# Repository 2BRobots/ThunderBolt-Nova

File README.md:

# ThunderBolt-Nova
Here can be found all the resources to build your own ThunderBolt development board. This board is based on the PIC18F14K50 microcontroller. It uses a bootloader so you can program it directly over USB without an ICSP programer. 
If you decide to make your own board you will need to burn the bootloader the firts time. You can use the 12Mhz or 48Mhz version, the hardware is the same for both versions.

Note: For the servo ports you must pay attention to the pin names in the botton of the board, not the top. Wiring in some servo models will require a modification. Also there is an error in silkscreen, in C5 servo port in the botton says "C2" instead of "C5". 
Be careful, this ports where designed to drive micro-servos. Using full size (8kg.cm or greater) servos can destroy the board due to excesive current flow, please use external power for the servos in this case.  

In this repositiry are all resources, examples and design files that will allow you to use all features of the board.

Here is a video of how to get started:

https://youtu.be/WCGcCIe8bug

Voltage Pinout:
GND = voltage ground.
EN  = this is the signal from the on/off switch, can be used for turn on/off addon boards.
VU  = this are the 5v from the USB port.
VB  = this is the voltage from the battery.
3V  = This is the regulated 3v output, it only can supply 200mA.

Also there is a shared pins for the internal LED (B7) and button (A3), this are used in the bootloader program but you can use it in your program too!!!  As an extra there is a voltage divider shared in the pin C6 (AN8) to measure the lipo battery voltage. 
For full diagram of conections and specs please see the board schematic and microcontroller datasheet. 

This board was designed to use a 1S litium battery (3.7v) and is equiped with an on board battery charger. Be careful when using one, wrong polarity can destroy your board!!!

Hope you find it useful and can make a lot of projects with it.

2B Robots (DAFR Electronics) invests time and resources providing this open source code and hardware, if you valorate our hard work please purchase our products and support us to continue creating more open source products!!!

Hardware licensed with Creative Commons BY-NC-SA.

Created by Daniel A. Fernandez Raygoza for 2B Robots.

Visit our online store: www.2brobots.com

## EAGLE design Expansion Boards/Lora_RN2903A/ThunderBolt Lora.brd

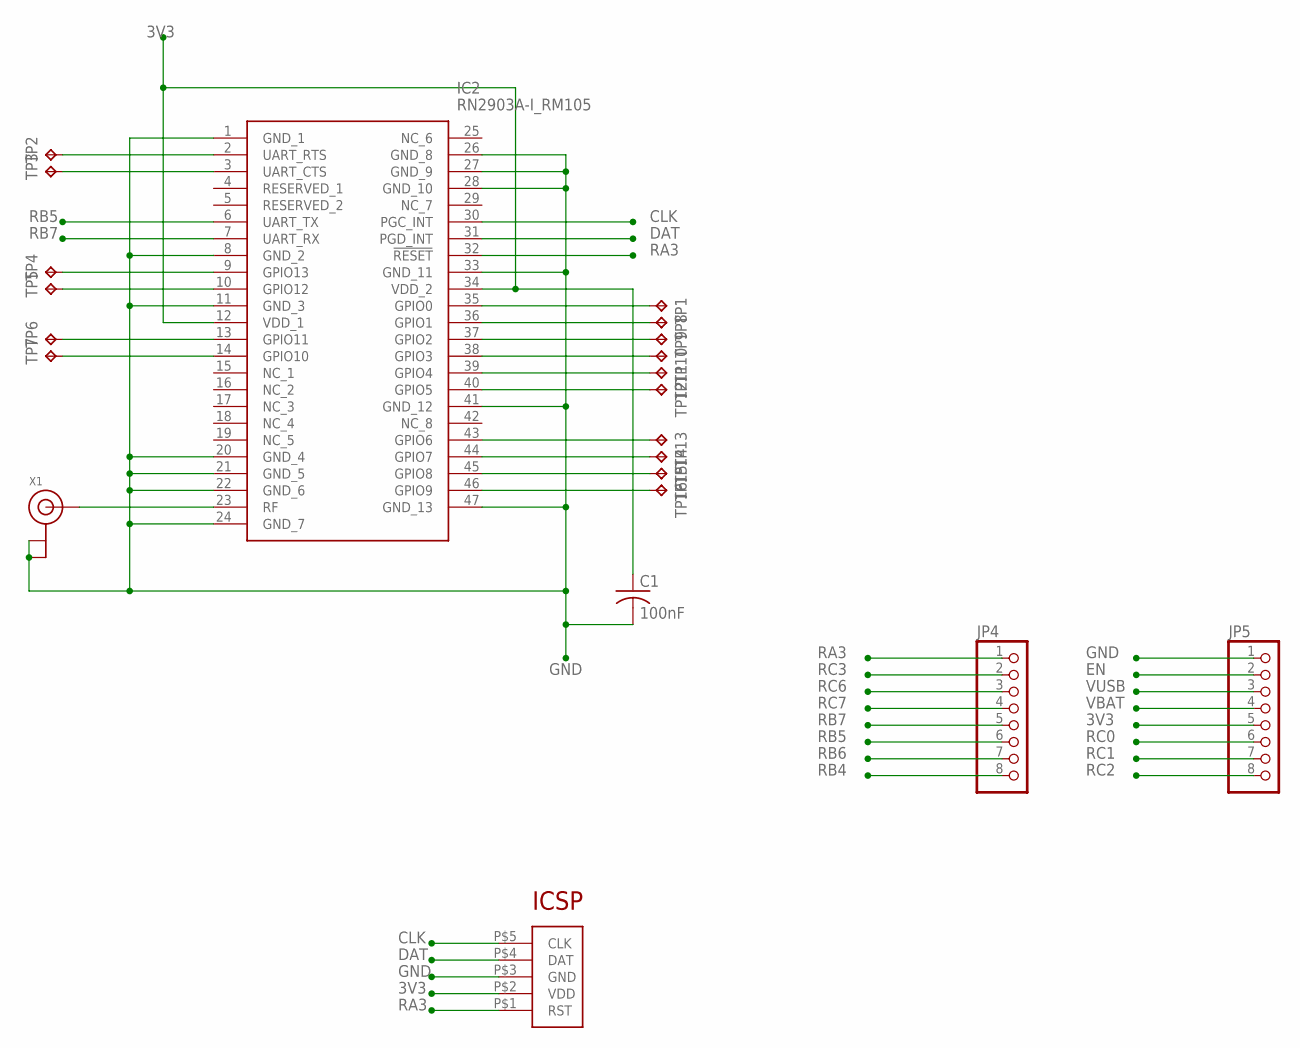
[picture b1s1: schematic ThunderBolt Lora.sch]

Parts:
C1: 100nF; C0603K
IC2: RN2903A-I_RM105; RN2903AIRM105
JP4, JP5: PINHD-1X8BIG; 1X08-BIG
TP1, TP2, TP3, TP4, TP5, TP6, TP7, TP8, TP9, TP10, TP11, TP12, TP13, TP14, TP15, TP16: TPB1,27; B1,27
U$2: ICSP_POGO
X1: ANTENNA_U.FL; U.FL

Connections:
3V3: C1.1, IC2.12 (VDD_1), IC2.34 (VDD_2), JP5.5, U$2.P$2 (VDD)
CLK: IC2.30 (PGC_INT), U$2.P$5 (CLK)
DAT: IC2.31 (PGD_INT), U$2.P$4 (DAT)
EN: JP5.2
GND: C1.2, IC2.1 (GND_1), IC2.8 (GND_2), IC2.11 (GND_3), IC2.20 (GND_4), IC2.21 (GND_5), IC2.22 (GND_6), IC2.24 (GND_7), IC2.26 (GND_8), IC2.27 (GND_9), IC2.28 (GND_10), IC2.33 (GND_11), IC2.41 (GND_12), IC2.47 (GND_13), JP5.1, U$2.P$3 (GND), X1.1 (GND), X1.2 (GND)
unnamed: IC2.2 (UART_RTS), TP2.TP
unnamed: IC2.3 (UART_CTS), TP3.TP
unnamed: IC2.9 (GPIO13), TP4.TP
unnamed: IC2.10 (GPIO12), TP5.TP
unnamed: IC2.23 (RF), X1.3 (SIGNAL)
unnamed: IC2.13 (GPIO11), TP6.TP
unnamed: IC2.14 (GPIO10), TP7.TP
unnamed: IC2.35 (GPIO0), TP1.TP
unnamed: IC2.46 (GPIO9), TP16.TP
unnamed: IC2.45 (GPIO8), TP15.TP
unnamed: IC2.44 (GPIO7), TP14.TP
unnamed: IC2.43 (GPIO6), TP13.TP
unnamed: IC2.40 (GPIO5), TP12.TP
unnamed: IC2.39 (GPIO4), TP11.TP
unnamed: IC2.38 (GPIO3), TP10.TP
unnamed: IC2.37 (GPIO2), TP9.TP
unnamed: IC2.36 (GPIO1), TP8.TP
RA3: IC2.32 (!RESET), JP4.1, U$2.P$1 (RST)
RB4: JP4.8
RB5: IC2.6 (UART_TX), JP4.6
RB6: JP4.7
RB7: IC2.7 (UART_RX), JP4.5
RC0: JP5.6
RC1: JP5.7
RC2: JP5.8
RC3: JP4.2
RC6: JP4.3
RC7: JP4.4
VBAT: JP5.4
VUSB: JP5.3

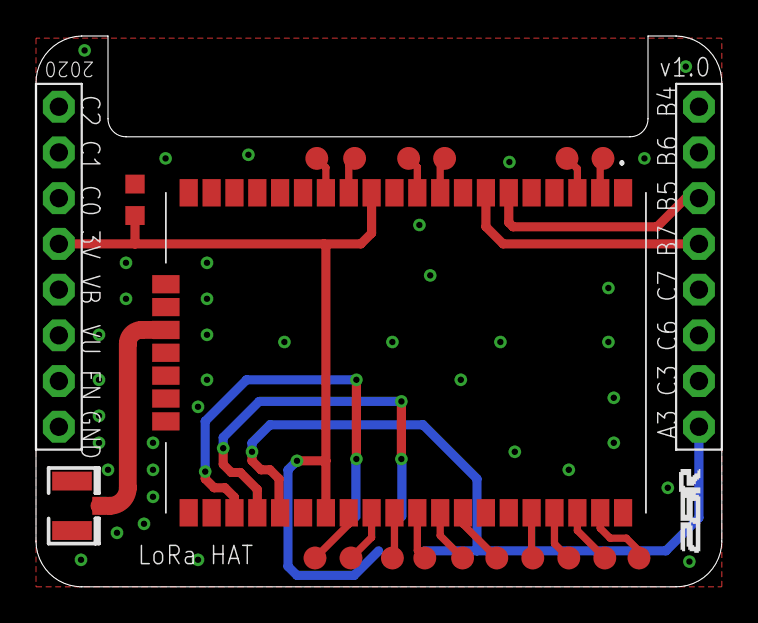
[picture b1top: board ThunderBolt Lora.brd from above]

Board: 2 copper layers, 38.1 x 30.6 mm, 22 parts (1 on the bottom side), 24 nets.

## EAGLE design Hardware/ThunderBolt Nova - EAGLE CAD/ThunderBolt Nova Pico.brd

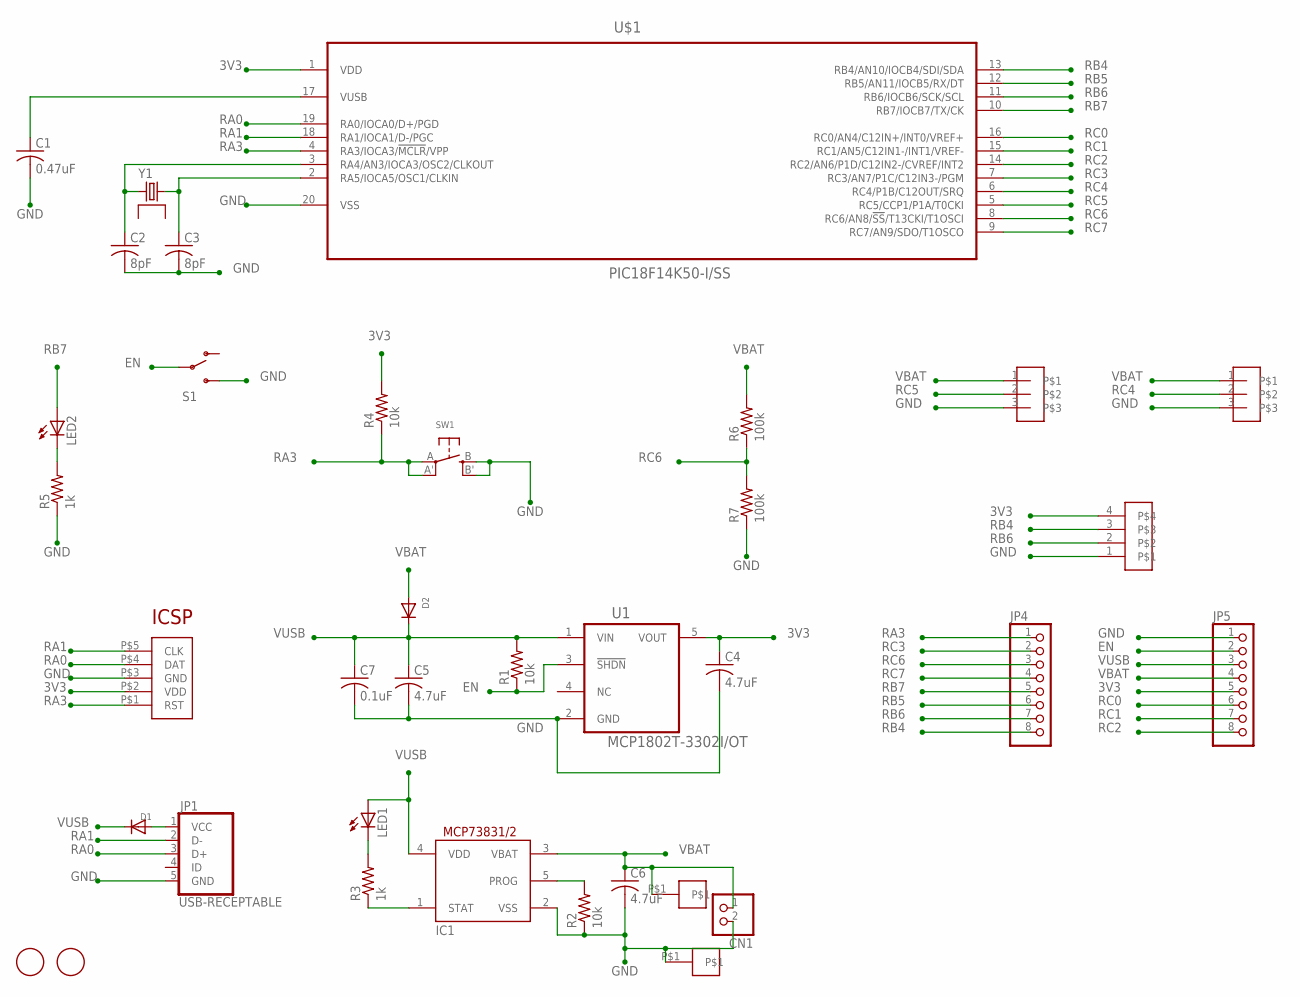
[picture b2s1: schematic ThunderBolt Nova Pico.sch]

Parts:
C1: 0.47uF; C0805K
C2, C3: 8pF; C0805K
C4, C5, C6: 4.7uF; C0805K
C7: 0.1uF; C0603K
CN1: JST_2PIN-SMT-RA; JST-PH-2-SMT-RA
D1, D2: DIODESOD-123; SOD-123
IC1: MCP73831/OT; SOT23-5L
JP1: USB-RECEPTABLE; FCI-10103594-0001LF
JP4, JP5: PINHD-1X8BIG; 1X08-BIG
LED1, LED2: LEDCHIPLED_1206; CHIPLED_1206
R1, R2, R4: 10k; R0805
R3, R5: 1k; R0805
R6, R7: 100k; R0805
S1: SWITCH-SPDT-SMD-A; SWITCH-SPST-SMD-A
SW1: SWITCH_TACT_SMT4.6X2.8; BTN_KMR2_4.6X2.8
U1: MCP1802T-3302I/OT; SOT95P270X145-5N
U$1: PIC18F14K50-I/SS; SOP65P780X200-20N
U$2: ICSP_POGO
U$3, U$4: PADSMD
U$5, U$6: PIN1X3
U$7: PIN1X4
U$8, U$9: FIDUCIAL; FIDUCIAL_1MM
Y1: GRX-330; OSC3225

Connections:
3V3: C4.1, JP5.5, R4.2, U1.5 (VOUT), U$1.1 (VDD), U$2.P$2 (VDD), U$7.4
EN: JP5.2, R1.1, S1.2, U1.3 (!SHDN)
GND: C1.2, C2.2, C3.2, C4.2, C5.2, C6.2, C7.2, CN1.2 (1), IC1.2 (VSS), JP1.5 (GND), JP5.1, R2.1, R5.1, R7.1, S1.3 (S), SW1.B (S), SW1.B' (S1), U1.2 (GND), U$1.20 (VSS), U$2.P$3 (GND), U$3.P$1, U$5.3, U$6.3, U$7.1
unnamed: C1.1, U$1.17 (VUSB)
unnamed: C2.1, U$1.3 (RA4/AN3/IOCA3/OSC2/CLKOUT), Y1.P$1 (1)
unnamed: C3.1, U$1.2 (RA5/IOCA5/OSC1/CLKIN), Y1.P$3 (3)
unnamed: D1.A, JP1.1 (VCC)
unnamed: IC1.1 (STAT), R3.1
unnamed: LED1.C, R3.2
unnamed: IC1.5 (PROG), R2.2
unnamed: LED2.C, R5.2
RA0: JP1.3 (D+), U$1.19 (RA0/IOCA0/D+/PGD), U$2.P$4 (DAT)
RA1: JP1.2 (D-), U$1.18 (RA1/IOCA1/D-/PGC), U$2.P$5 (CLK)
RA3: JP4.1, R4.1, SW1.A, SW1.A' (P1), U$1.4 (RA3/IOCA3/!MCLR!/VPP), U$2.P$1 (RST)
RB4: JP4.8, U$1.13 (RB4/AN10/IOCB4/SDI/SDA), U$7.3
RB5: JP4.6, U$1.12 (RB5/AN11/IOCB5/RX/DT)
RB6: JP4.7, U$1.11 (RB6/IOCB6/SCK/SCL), U$7.2
RB7: JP4.5, LED2.A, U$1.10 (RB7/IOCB7/TX/CK)
RC0: JP5.6, U$1.16 (RC0/AN4/C12IN+/INT0/VREF+)
RC1: JP5.7, U$1.15 (RC1/AN5/C12IN1-/INT1/VREF-)
RC2: JP5.8, U$1.14 (RC2/AN6/P1D/C12IN2-/CVREF/INT2)
RC3: JP4.2, U$1.7 (RC3/AN7/P1C/C12IN3-/PGM)
RC4: U$1.6 (RC4/P1B/C12OUT/SRQ), U$5.2
RC5: U$1.5 (RC5/CCP1/P1A/T0CKI), U$6.2
RC6: JP4.3, R6.1, R7.2, U$1.8 (RC6/AN8/!SS!/T13CKI/T1OSCI)
RC7: JP4.4, U$1.9 (RC7/AN9/SDO/T1OSCO)
VBAT: C6.1, CN1.1 (2), D2.A, IC1.3 (VBAT), JP5.4, R6.2, U$4.P$1, U$5.1, U$6.1
VUSB: C5.1, C7.1, D1.C, D2.C, IC1.4 (VDD), JP5.3, LED1.A, R1.2, U1.1 (VIN)

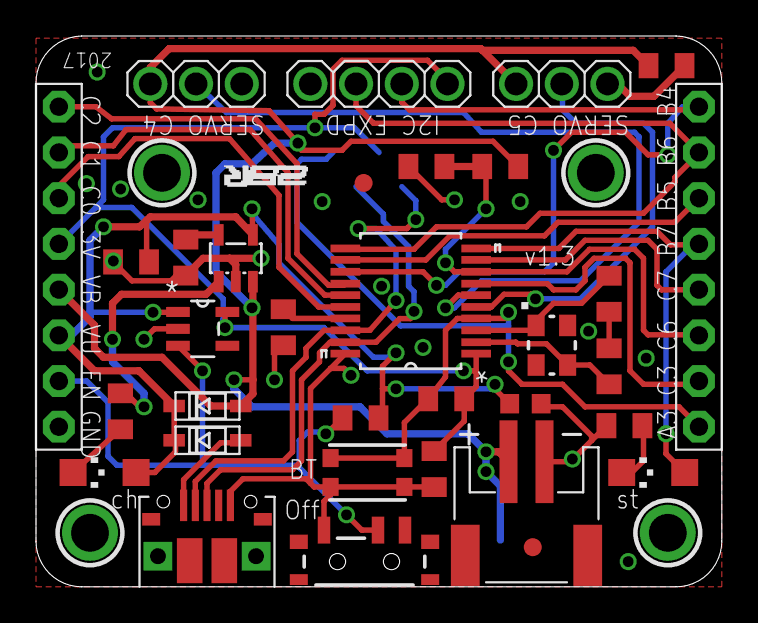
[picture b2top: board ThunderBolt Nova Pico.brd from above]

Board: 2 copper layers, 38.1 x 30.6 mm, 36 parts (1 on the bottom side), 28 nets.

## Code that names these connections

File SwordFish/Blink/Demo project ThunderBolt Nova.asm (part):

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ANS10 = 2
ANS11 = 3
; PORTA
RA0 = 0
RA1 = 1
RA3 = 3
RA4 = 4
RA5 = 5
AN3 = 4
OSC2 = 4
OSC1 = 5
CLKOUT = 4
CLKIN = 5
; PORTB
RB4 = 4
RB5 = 5
RB6 = 6
RB7 = 7
SDI = 4
RX = 5
SCL = 6
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AN10 = 4
AN11 = 5
; PORTC
RC0 = 0
RC1 = 1
RC2 = 2
RC3 = 3
RC4 = 4
RC5 = 5
RC6 = 6
RC7 = 7
AN4 = 0
AN5 = 1
AN6 = 2
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; DDRA
TRISA4 = 4
TRISA5 = 5
RA4 = 4
RA5 = 5
; TRISA
TRISA4 = 4
TRISA5 = 5
RA4 = 4
RA5 = 5
; DDRB
TRISB4 = 4
TRISB5 = 5
TRISB6 = 6
TRISB7 = 7
RB4 = 4
RB5 = 5
RB6 = 6
RB7 = 7
; TRISB
TRISB4 = 4
TRISB5 = 5
TRISB6 = 6
TRISB7 = 7
RB4 = 4
RB5 = 5
RB6 = 6
RB7 = 7
; DDRC
TRISC0 = 0
TRISC1 = 1
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TRISC5 = 5
TRISC6 = 6
TRISC7 = 7
RC0 = 0
RC1 = 1
RC2 = 2
RC3 = 3
RC4 = 4
RC5 = 5
RC6 = 6
RC7 = 7
; TRISC
TRISC0 = 0
TRISC1 = 1
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TRISC5 = 5
TRISC6 = 6
TRISC7 = 7
RC0 = 0
RC1 = 1
RC2 = 2
RC3 = 3
RC4 = 4
RC5 = 5
RC6 = 6
RC7 = 7
; OSCTUNE
SPLLEN = 6
INTSRC = 7
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
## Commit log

2017-05-20 examples added
2017-06-17 added examples
2017-08-18 corrections in examples
2017-08-26 added example
2017-09-10 added interrupt example
    code for mikroC
2018-03-30 Add usb serial tool
2018-03-30 Typo correction
2020-08-20 Lora shield

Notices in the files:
SwordFish/Blink/Demo project ThunderBolt Nova.asm:
Version 1.1.6.3 SE Copyright Mecanique 2013
parts and their libraries:
golledge_full_v1-0: © Golledge Electronics Ltd 2015. Released under GNU General Public License. Full library V1.0.
SparkFun-Electromechanical: Licensing: Creative Commons ShareAlike 4.0 International - https://creativecommons.org/licenses/by-sa/4.0
